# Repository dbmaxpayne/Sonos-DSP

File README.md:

# Sonos-DSP
Make Sonos Play:5 Gen. 1 recycle-mode speakers sing again

# Introduction
This project stems from four Sonos Play:5 that I acquired unbeknownst of the so called Recycle Mode which basically bricked the devices intenionally by Sonos after offering a 30% discount on the newer Gen 2 speakers to the original owner.
Of course the original owner did not tell me that he underwent this process and so I used the speakers as basic line-in devices for about six months.
From one day to another they all four stopped working.
Upon installing the Sonos app and trying to see what was wrong, I got the message that they were in Recycle Mode and could not be set-up again.
I was like "what?!" and consulted the internet for help.
Quickly it turned out that a lot of customers were angry about the same thing and that Sonos actually stopped bricking the devices after some pressure from the community and also because they were deliberately making rubbish out of perfectly good hardware.
However, the official statement was (and still is in 10.2023), that bricked devices remain bricked.
I contacted Sonos about this twice and tried to acquire a reset firmware so I could use line-in again.
They were as helpful as you'd expect for a company that does not offer repairs or schematics and thinks of a recycle mode for working hardware...

Having spent some money on the devices I was obviously not pleased and tried to find a way around this.
This repo is the result of my work and I hope it helps anyone with old Play:5s or even other devices to make them sing again :)

>[!WARNING]
>Disclaimer: All information in this repo is delivered as a courtesy. Please think about what you do as I do not take any responsibility for destroying your devices or your health.
>Remember: Electricity is dangerous and there is a risk of suffering an electric shock when opening these devices.

> [!NOTE]
> You can find datasheets in the corresponding subfolder.
> These are mostly not done by me and have all rights reserved to their creators.

# General Information
## Needed hard- and software
- Sonos Play:5 Speaker (obviously)
- Analog Devices ADAU1701-based Audio DSP board
  - e.g. Wondom APM2 (I used this for my initial tests - worked really well)
  - e.g. Cheap ADAU1401/1701-based development board from AliExpress
  - (USB programmer for the DSP board. e.g. Wondom ICP1) [This can be replaced by a TCPIP programmer like this one [blus-audio/sigmadsp](https://github.com/blus-audio/sigmadsp)]
- Raspberry Pi or similar SBC / Microcontroller. I recommend a Zero W or Zero 2 W
- Shielded wires for I2S digital sound data (e.g. RG178 coax cable). You might get away without them or a ferrite, too.
- Alternatively: Use the provided PCB layout to make a PCB yourself. I did this at pcbway.com and was very happy with their quality.
  - 2x20 2.54mm Female Pin Header
  - 2x25 2.00mm Female Pin Header
  - Single Row 2.54mm Female and Male Pin Headers
  - Micro JST 10Pin 1.25mm Connector (You can also desolver the one on the Sonos logic board)
- Breadboard cables
- MP1584EN DC-DC Step-Down Converter to Power the RPi and ADAU1401/1701 DSP
- 20k resistor
- BC327-40 Transistor
- Soldering Iron
- Analog Devices SigmaStudio (to program the DSP)
  
## Sonos Play:5 Mainboard Connector Pinout
| Mainboard Pin # | Function | Function                  | Mainboard Pin # |
| :---            |:---      |:---                       | :---            |
| 1               | GND      |                           | 2               |
| 3               | GND      |                           | 4               |
| 5               | GND      |                           | 6               |
| 7               | GND      | +3.3V                     | 8               |
| 9               | GND      | +3.3V                     | 10              |
| 11              | GND      | +3.3V                     | 12              |
| 13              | GND      | +11.1V                    | 14              |
| 15              | GND      | +12V                      | 16              |
| 17              | GND      | Amplifier Power Enable    | 18              |
| 19              | GND      |                           | 20              |
| 21              | GND      |                           | 22              |
| 23              | GND      |                           | 24              |
| 25              | GND      |                           | 26              |
| 27              | GND      | DAI_SCLK / DAI_MCLK (I2S) | 28              |
| 29              | GND      |                           | 30              |
| 31              | GND      | DAI_LRCK (I2S)            | 32              |
| 33              | GND      | DAI_SDIN1 (I2S)           | 34              |
| 35              | GND      | SCL (I2C)                 | 36              |
| 37              | GND      | SDA (I2C)                 | 38              |
| 39              | GND      | INT                       | 40              |
| 41              | GND      | RST#                      | 42              |
| 43              | GND      | MUTE#                     | 44              |
| 45              |          |                           | 46              |
| 47              |          |                           | 48              |
| 49              |          |                           | 50              |

## Sonos Play:5 Button Connector
- Pin 1 is identified on the logic board by a white dot
- There is no need for LED resisors. These are on the button board if you use 3.3V
> [!WARNING]
> Do not drive the LEDs directly off GPIO pins. These are not strong enough!

| Pin # | Function   |
| :---  | :---       |
| 1     | Unknown    |
| 2     | Mute       |
| 3     | LED Green  |
| 4     | LED Red    |
| 5     | GND        |
| 6     | LED Orange |
| 7     | GND        |
| 8     | LED White  |
| 9     | Volume +   |
| 10    | Volume -   |

# Wiring
> [!NOTE]
> Use shielded wires for all I2S lines or at least keep them as short as possible.
> Maybe you can use unshielded wires with a ferrite. I have not tried this.
> The CS44600 is very picky about correct clocks and has an automatic sampling rate selector built-in.
> If you use normal breadboard connectors you will most likely NOT get it working as we are working with a very high frequency of 12.288 Mhz which is 12.228 Million pulses per second.
> In my original test design I used two breadboard cables. One was stripped of its insulating and then wrapped in aluminium foil with the second data wire inside.
> This outher shield was then connected to GND.
> Don't forget to insulate it again with some sticky tape or heat shrink tubes.
> This worked well, but the cables were very stiff.
> I switched to RG178 coax wire which I bought off AliExpress for like 8€/10m.
>
> After my initial tests I designed a simple drop-in PCB that removes the need of these complex wire designs.
> You can find the PCB design on this page, too.

## Main Wiring
| Sonos Mainboard Pin #          | DSP Pin            | Raspberry Pi GPIO #        |
| :---                           |:---                |:---                        |
| 28 - DAI_SCLK / DAI_MCLK (I2S) | MP11 - Out_BCLK    | GPIO 18 - I2S CLK In       |
| 32 - DAI_LRCK (I2S)            | MP10 - Out_LRCLK   | GPIO 19 - I2S LRCLK        |
| 34 - DAI_SDIN1 (I2S)           | MP6 - TDM_DATA_OUT |                            |
|                                | MP0 - TDM_DATA_IN  | GPIO 21 - I2S Data Out     |
| 36 - SCL (I2C)                 | (SCL)              | GPIO  3 - I2C SCL          |
| 38 - SDA (I2C)                 | (SDA)              | GPIO  2 - I2C SCL          |
| 42 - RST#                      |                    | GPIO 17                    |
| 44 - MUTE#                     |                    | GPIO 5                     |
| 28 - Amplifier Power Enable    |                    | GPIO 5 (Yes, connect both) |
|                                | WP                 | GPIO 26                    |
| GND                            | GND                | GND                        |

## Button Wiring
| Pin           | DSP Pin | Raspberry Pi GPIO # |
| :---          | :---    | :---                |
| 2 - Mute      |         | GPIO 6              |
| 5 OR 7 - GND  | GND     |                     |
| 9 - Volume +  | MP1     |                     |
| 10 - Volume - | MP7     |                     |

# Software / RPi Configuration
## Sonos-Control.sh
```
Sonos-Control.sh must be called to set the CS44600's registers to allow audio to pass through the signal path and to do various other things.
Check the file as it contains comments.

install:
The most important command as it will set up everything for you on a freshly installed Raspberry Pi.
It also sets up basic Bluetooth functionality.
Be aware of the fact that Bluetooth is not perfect on RPi Zero 1's.
It works for me, but it might not work for you.

initialize:
As the name suggests, this argument initializes the CS44600 after a reboot.
A series of register writes ensures proper operation of the chip.
Consult the datasheet for detailed explanation or custom settings.

getStatus:
Read all important registers of CS44600 to see if the initialization has worked.

switchMute:
Switches the mute state of the hardware and sends a signal to a possible squeezelite server to pause/resume playback.
As pin 44 and 28 of the Sonos mainboard are to be connected, it also switches on the power output stage of the board.
If pin 28 is not set to high, the volume will be very low and the speakers are basically driven from a 5V instead of a 24V source. 
```

# HowTo
- Wire everything. Maybe leave out the buttons in the beginning and everything else that complicates things
- Alternatively use my PCB layout
- Copy the folder Sonos-Control onto the RPi
- chmod +x Sonos-Control.sh
- Run Sonos-Control.sh install
- If this is the first time you do this, say yes when asked to flash the firmware. This will flash the ADAU1401/1701's firmware so we have a usable base.
- Cut the power and reboot everything
- Run 'speaker-test -t wav -c 2' and hope that you hear a sound
- If not there is probably something wrong with your wiring. Remember to use shielded wires for all I2S wires and keep them as short as possible.
  - Debug with `pigs i2cri 0 0x2a 1` and look at the ADAU1701's datasheet. This register tells you if CS44600 was able to achieve a lock to the I2S bitclocks provided by ADAU1701.
    If the SRC_UNLOCK bit is set, something is not right. If SRC_LOCK is set, but you can't hear anything, the wirings of DAI_MCLK & DAI_LRCLK are correct and the problem is either at DAI_SDIN1 or your SigmaStudio project not outputting anything.
  - You can also use piscope to see if the I2S signals are generated correctly. For this stop the pigpiod service 'sudo systemctl stop pigpiod' and run it with slightly different settings: 'sudo pigpiod -s 2 -t 0'
  Connect via SSH with X11 forwarding and run 'piscope &'

To make changes to the DSP (like change the crossover frequency or enable bass boost)
- Load Sonos-DSP.dspproj into SigmaStudio
- On 'Hardware Configuration\Config' right click on TCPIP1701, select 'Show TCPI/IP settings' and set the IP address.
- Click on 'Link Compile Download'. This will transfer the compiled program to the RPi and sigmadsp will write it to the RAM of the DSP (this is NOT permanent).
- You can now make changes to everything pretty much live.
- When everything is as you want it, go back to 'Hardware Configuration\Config' and connect the ADAU1701 IC 1 to the 'USB Interface'. Then right click the IC 1 and select 'Write latest compilation to EEPROM'.
- This will create the firmware files in a subfolder called 'Sonos-DSP_IC 2'
- Now run the PowerShell script Convert-SigmaStudioBinToEcometHex.ps1 on the corresponding bin file. This will convert it to the necessary format to flash it to the DPS's EEPROM.
- Copy the file to RPi and place it in the folder 'Sonos-Control'. The name must be 'E2Prom.pshex'. Then run 'Sonos-Control.sh writeE2PROM' which will flash it.

# Special Thanks
This project would not have been successfull without the following:
- https://sites.google.com/site/sonosdebug
- https://github.com/mamin27/ecomet_i2c_raspberry_tools
- https://github.com/blus-audio/sigmadsp
- https://github.com/JasonLG1979/PiZero-Bluetooth-Audio-Receiver

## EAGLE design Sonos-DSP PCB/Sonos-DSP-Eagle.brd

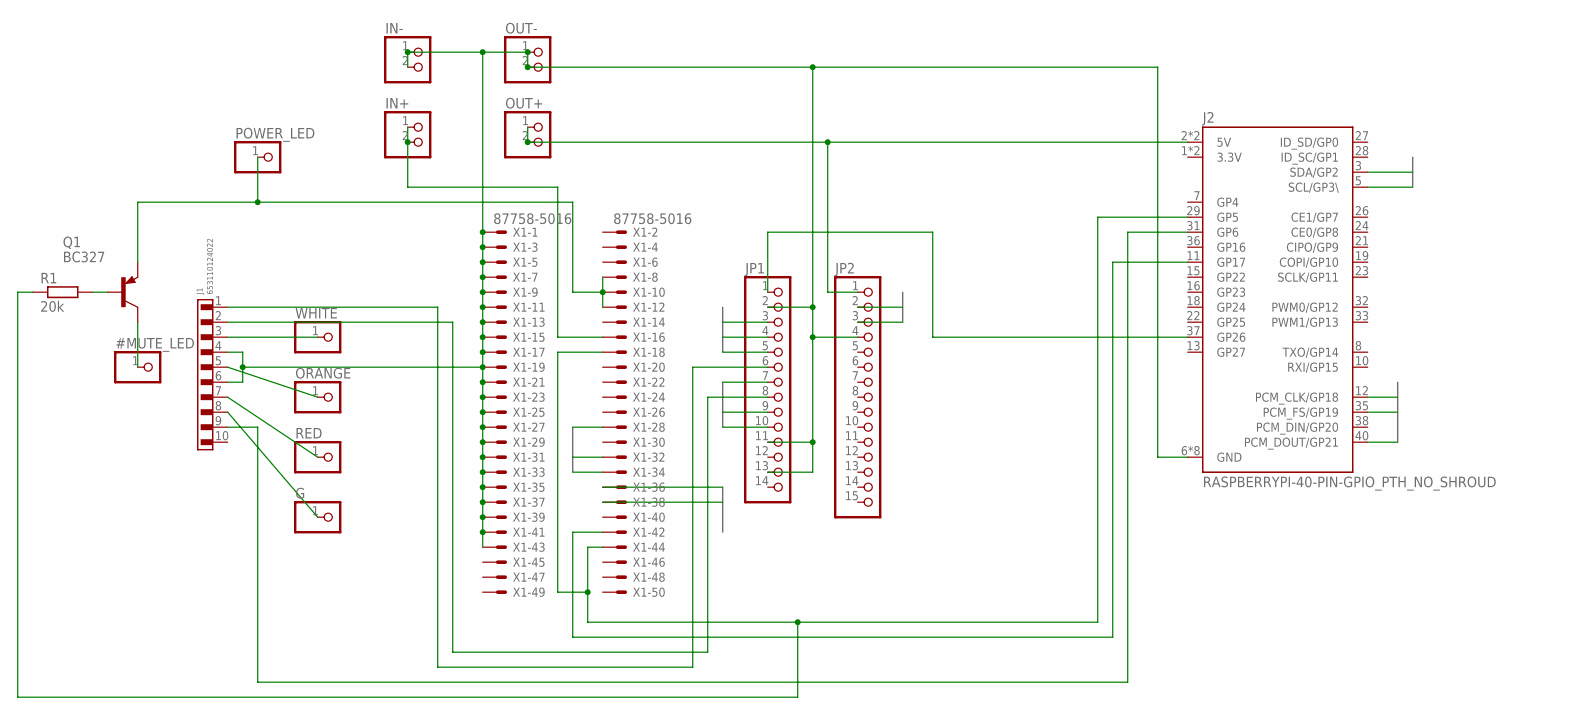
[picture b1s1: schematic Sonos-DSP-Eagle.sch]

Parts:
#MUTE_LED: PINHD-1X1; 1X01
G: PINHD-1X1; 1X01
IN+: PINHD-1X2; 1X02
IN-: PINHD-1X2; 1X02
J1: 653110124022
J2: RASPBERRYPI-40-PIN-GPIO_PTH_NO_SHROUD; 2X20
JP1: PINHD-1X14; 1X14
JP2: PINHD-1X15; 1X15
ORANGE: PINHD-1X1; 1X01
OUT+: PINHD-1X2; 1X02
OUT-: PINHD-1X2; 1X02
POWER_LED: PINHD-1X1; 1X01
Q1: BC327; TO92-EBC
R1: 20k; 0204V
RED: PINHD-1X1; 1X01
WHITE: PINHD-1X1; 1X01
X1: 87758-5016

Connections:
3.3V: J2.1 (3.3V), J2.17 (3.3V)
5V: J2.2 (5V), J2.4 (5V), JP2.1, OUT+.1, OUT+.2
+3.3V-SONOS: POWER_LED.1, Q1.E, X1.8, X1.10, X1.12
+12V: IN+.1, IN+.2, X1.16
CLK: J2.12 (PCM_CLK/GP18), JP1.3, JP1.9, X1.28
D_TORPI: J2.40 (PCM_DOUT/GP21), JP1.7
D_TOSONOS: JP1.5, X1.34
FS: J2.35 (PCM_FS/GP19), JP1.4, JP1.10, X1.32
GND: IN-.1, IN-.2, J1.4, J1.6, J2.6 (GND), J2.9 (GND), J2.14 (GND), J2.20 (GND), J2.25 (GND), J2.30 (GND), J2.34 (GND), J2.39 (GND), JP1.2, JP1.11, JP1.13, JP2.4, OUT-.1, OUT-.2, X1.1, X1.3, X1.5, X1.7, X1.9, X1.11, X1.13, X1.15, X1.17, X1.19, X1.21, X1.23, X1.25, X1.27, X1.29, X1.31, X1.33, X1.35, X1.37, X1.39, X1.41, X1.43
LED_GREEN: G.1, J1.8
LED_ORANGE: J1.5, ORANGE.1
LED_RED: J1.7, RED.1
LED_WHITE: J1.3, WHITE.1
MUTE#: J2.29 (GP5), R1.1, X1.18, X1.44
MUTE_BTN: J1.9, J2.31 (GP6)
unnamed: Q1.B, R1.2
unnamed: #MUTE_LED.1, Q1.C
RST#: J2.11 (GP17), X1.42
SCL: J2.5 (SCL/GP3\), JP2.3, X1.36
SDA: J2.3 (SDA/GP2), JP2.2, X1.38
VOL+: J1.2, JP1.8
VOL-: J1.1, JP1.6
WP: J2.37 (GP26), JP1.1

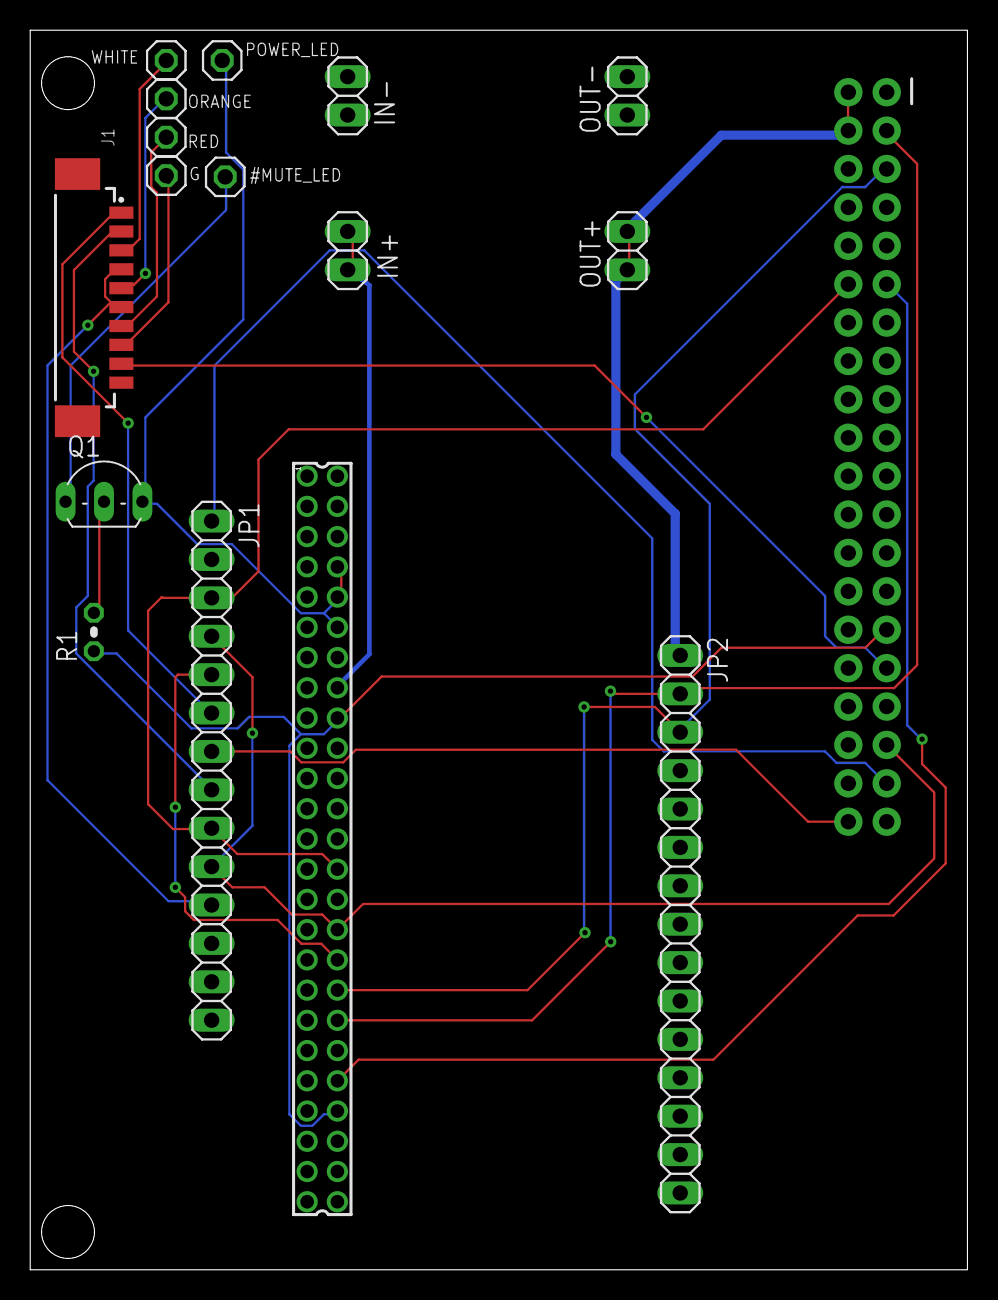
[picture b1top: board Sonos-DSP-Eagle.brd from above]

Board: 2 copper layers, 62.0 x 82.0 mm, 17 parts (1 on the bottom side), 23 nets.

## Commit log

2024-05-27 Create \home
2024-05-27 Create home

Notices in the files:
parts and their libraries:
Wurth_Connectors_WR-WTB: Copyright: Würth Elektronik
SparkFun-Connectors: Licensing: Creative Commons ShareAlike 4.0 International - https://creativecommons.org/licenses/by-sa/4.0
